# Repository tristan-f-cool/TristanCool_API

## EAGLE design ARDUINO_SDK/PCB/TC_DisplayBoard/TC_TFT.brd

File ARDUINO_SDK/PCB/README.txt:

$$$$$$$$$$$$$$$$$$$$$$$$$$$$$$$$$$$$$$$$$$$$$$$$$$$$$$$$$$$$$$$$$$$$$$$$$$$$$$$$$$$$$$$$$
$		     		Tristan Cool Master API 				$
$	            	         PCB Proto Dev board					$
$				     Arduino SDK					$
$$$$$$$$$$$$$$$$$$$$$$$$$$$$$$$$$$$$$$$$$$$$$$$$$$$$$$$$$$$$$$$$$$$$$$$$$$$$$$$$$$$$$$$$$
...\TristanCool_API\ARDUINO_SDK\PCB

_________________________________________________________________________________________
~~~ VERSION ~~~~~ DATE ~~~~~~~~ AUTHOR ~~~~~~~~~~~~~~~~~~~ NOTE ~~~~~~~~~~~~~~~~~~~~~~~~~
_________________________________________________________________________________________
     0.0       2020_10_17	Tristan Cool		Initial project creation

_________________________________________________________________________________________

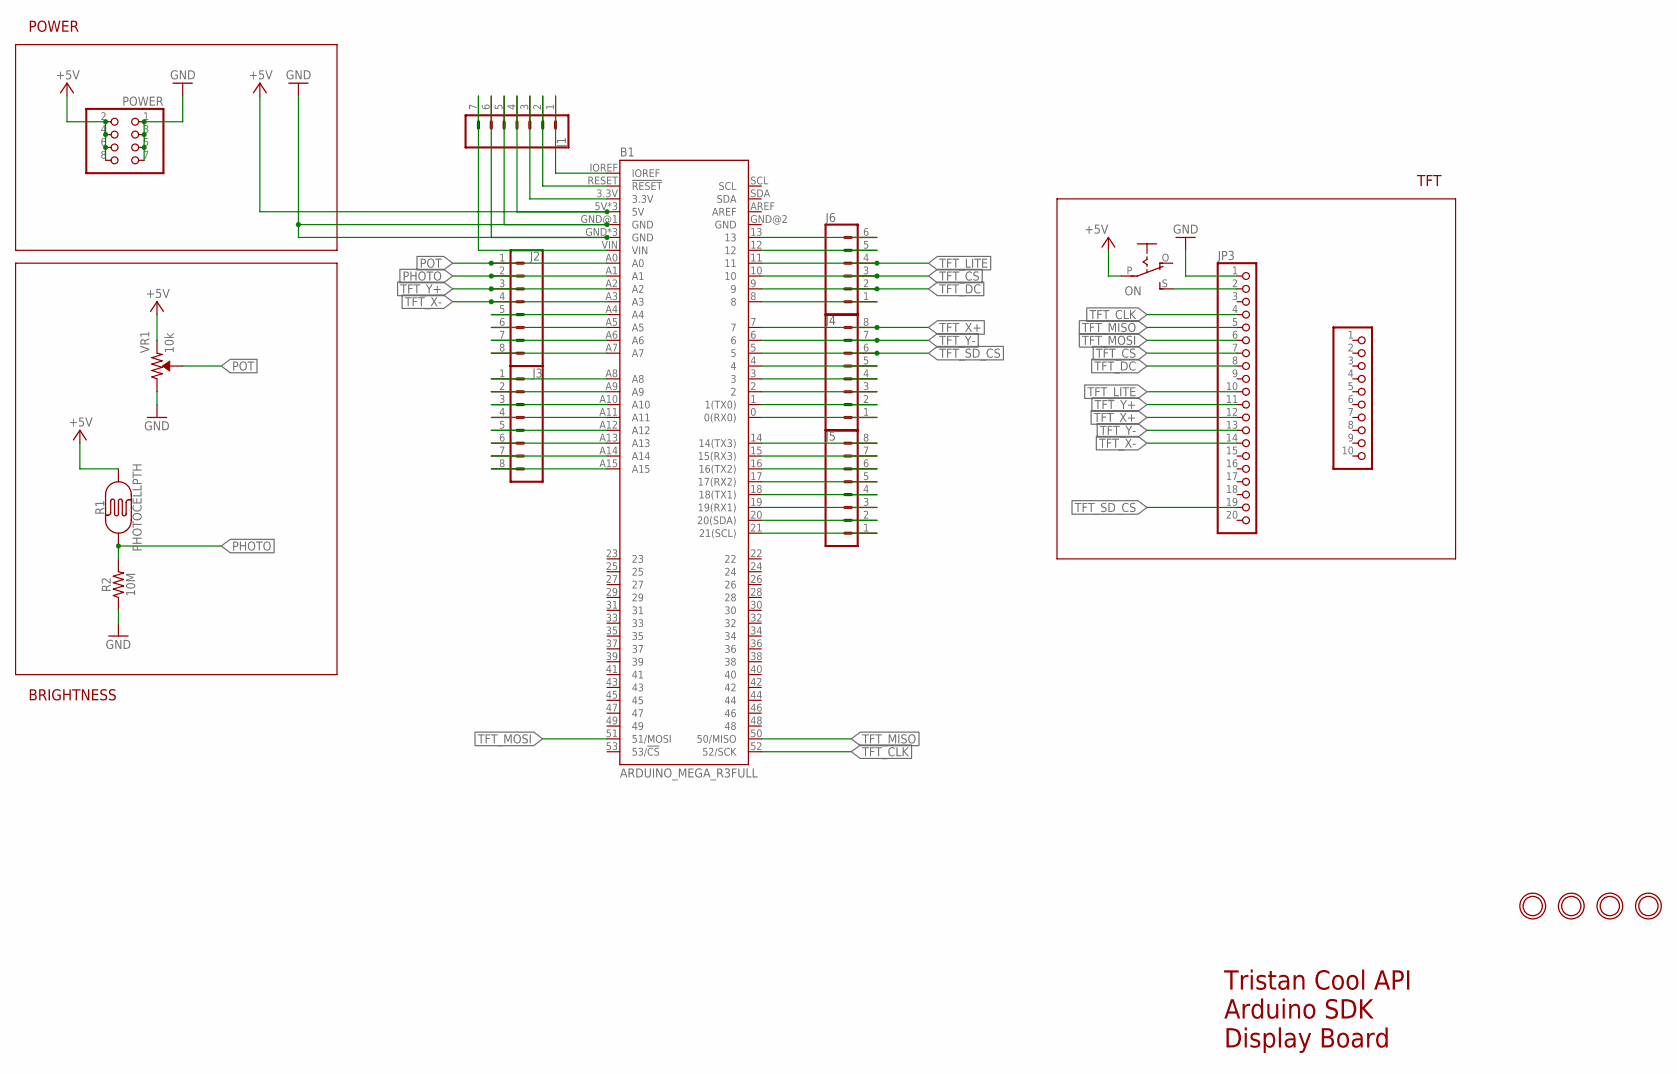
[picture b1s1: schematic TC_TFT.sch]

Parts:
B1: ARDUINO_MEGA_R3FULL; ARDUINO_MEGA_NO_SILK
J1: CONN_07; 1X07
J2, J3, J4, J5: CONN_08"; 1X08
J6: CONN_06SILK_FEMALE_PTH; 1X06
JP3: HEADER-1X20ROUND; 1X20_ROUND
ON: EG1218S; EG1218
POWER: PINHD-2X4; 2X04
R1: PHOTOCELLPTH; PHOTOCELL
R2: 10M; 0603
U$1, U$2, U$3, U$4: MOUNTINGHOLE3.0THIN; MOUNTINGHOLE_3.0_PLATEDTHIN
U$5: PINHD-1X10; 1X10-BIG
VR1: 10k; TRIMPOT-PTH-3386U

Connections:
+5V: B1.5V, B1.5V@1 (5V), B1.5V@2 (5V), J1.4, ON.P, POWER.2, POWER.4, POWER.6, POWER.8, R1.2, VR1.1 (CCW)
GND: B1.GND, B1.GND@1 (GND), B1.GND@3 (GND), B1.GND@4 (GND), J1.5, J1.6, JP3.1, POWER.1, POWER.3, POWER.5, POWER.7, R2.1, VR1.3 (CW)
unnamed: JP3.2, ON.S
unnamed: B1.IOREF, J1.1
unnamed: B1.RESET (!RESET), J1.2
unnamed: B1.3.3V, J1.3
unnamed: B1.VIN, J1.7
unnamed: B1.A4, J2.5
unnamed: B1.A5, J2.6
unnamed: B1.A6, J2.7
unnamed: B1.A7, J2.8
unnamed: B1.A8, J3.1
unnamed: B1.A9, J3.2
unnamed: B1.A10, J3.3
unnamed: B1.A11, J3.4
unnamed: B1.A12, J3.5
unnamed: B1.A13, J3.6
unnamed: B1.A14, J3.7
unnamed: B1.A15, J3.8
unnamed: B1.8, J6.1
unnamed: B1.12, J6.5
unnamed: B1.13, J6.6
unnamed: B1.4, J4.5
unnamed: B1.3, J4.4
unnamed: B1.2, J4.3
unnamed: B1.1 (1(TX0)), J4.2
unnamed: B1.0 (0(RX0)), J4.1
unnamed: B1.14 (14(TX3)), J5.8
unnamed: B1.15 (15(RX3)), J5.7
unnamed: B1.16 (16(TX2)), J5.6
unnamed: B1.17 (17(RX2)), J5.5
unnamed: B1.18 (18(TX1)), J5.4
unnamed: B1.19 (19(RX1)), J5.3
unnamed: B1.20 (20(SDA)), J5.2
unnamed: B1.21 (21(SCL)), J5.1
PHOTO: B1.A1, J2.2, R1.1, R2.2
POT: B1.A0, J2.1, VR1.2 (WIPER)
TFT_CLK: B1.52 (52/SCK), JP3.4
TFT_CS: B1.10, J6.3, JP3.7
TFT_DC: B1.9, J6.2, JP3.8
TFT_LITE: B1.11, J6.4, JP3.10
TFT_MISO: B1.50 (50/MISO), JP3.5
TFT_MOSI: B1.51 (51/MOSI), JP3.6
TFT_SD_CS: B1.5, J4.6, JP3.19
TFT_X+: B1.7, J4.8, JP3.12
TFT_X-: B1.A3, J2.4, JP3.14
TFT_Y+: B1.A2, J2.3, JP3.11
TFT_Y-: B1.6, J4.7, JP3.13

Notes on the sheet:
POWER
BRIGHTNESS
TFT
Tristan Cool API Arduino SDK Display Board

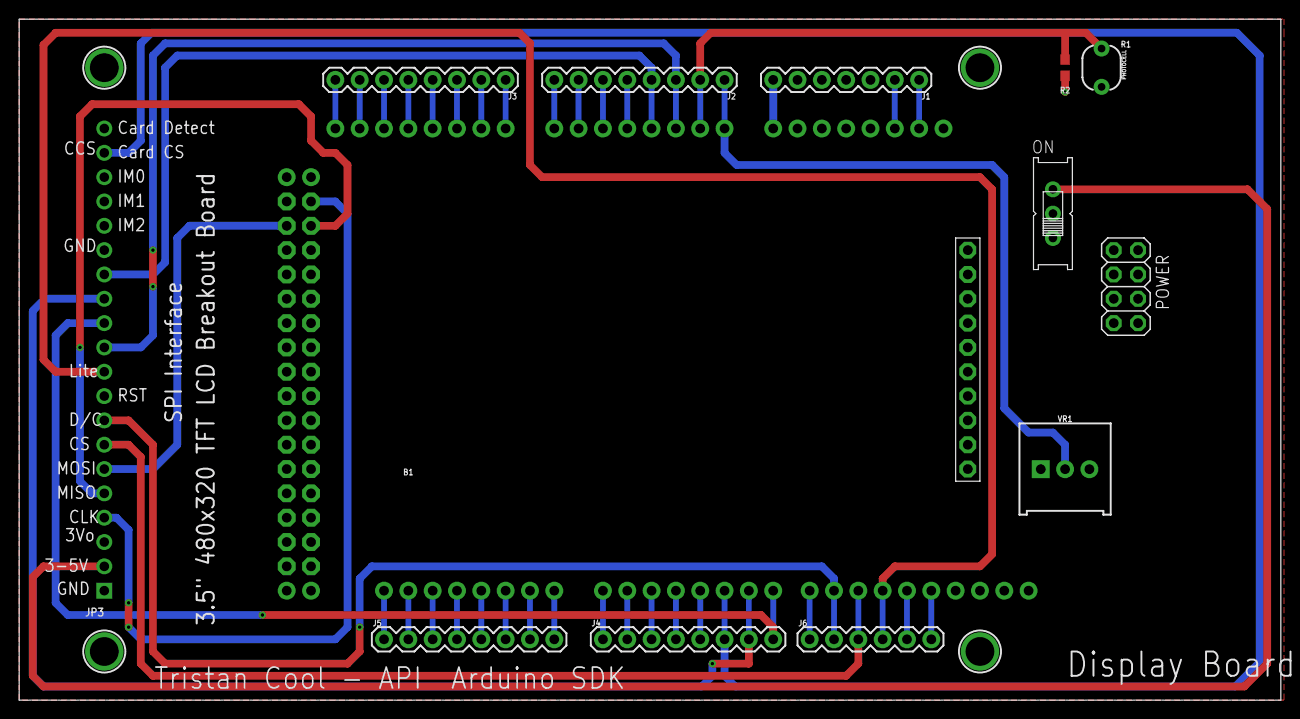
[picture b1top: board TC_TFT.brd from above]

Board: 2 copper layers, 131.8 x 71.1 mm, 18 parts (0 on the bottom side), 48 nets.

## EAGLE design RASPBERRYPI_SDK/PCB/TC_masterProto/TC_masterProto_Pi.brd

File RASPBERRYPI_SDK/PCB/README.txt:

$$$$$$$$$$$$$$$$$$$$$$$$$$$$$$$$$$$$$$$$$$$$$$$$$$$$$$$$$$$$$$$$$$$$$$$$$$$$$$$$$$$$$$$$$
$		     		Tristan Cool API PCB					$
$	            	      Master PCB Proto Dev board				$
$			          Raspberry PI SDK					$
$$$$$$$$$$$$$$$$$$$$$$$$$$$$$$$$$$$$$$$$$$$$$$$$$$$$$$$$$$$$$$$$$$$$$$$$$$$$$$$$$$$$$$$$$
...\TristanCool_API\RASPBERRYPI_SDK\PCB

_________________________________________________________________________________________
~~~ VERSION ~~~~~ DATE ~~~~~~~~ AUTHOR ~~~~~~~~~~~~~~~~~~~ NOTE ~~~~~~~~~~~~~~~~~~~~~~~~~
_________________________________________________________________________________________
     0.0       2020_10_17	Tristan Cool		Initial project creation

_________________________________________________________________________________________

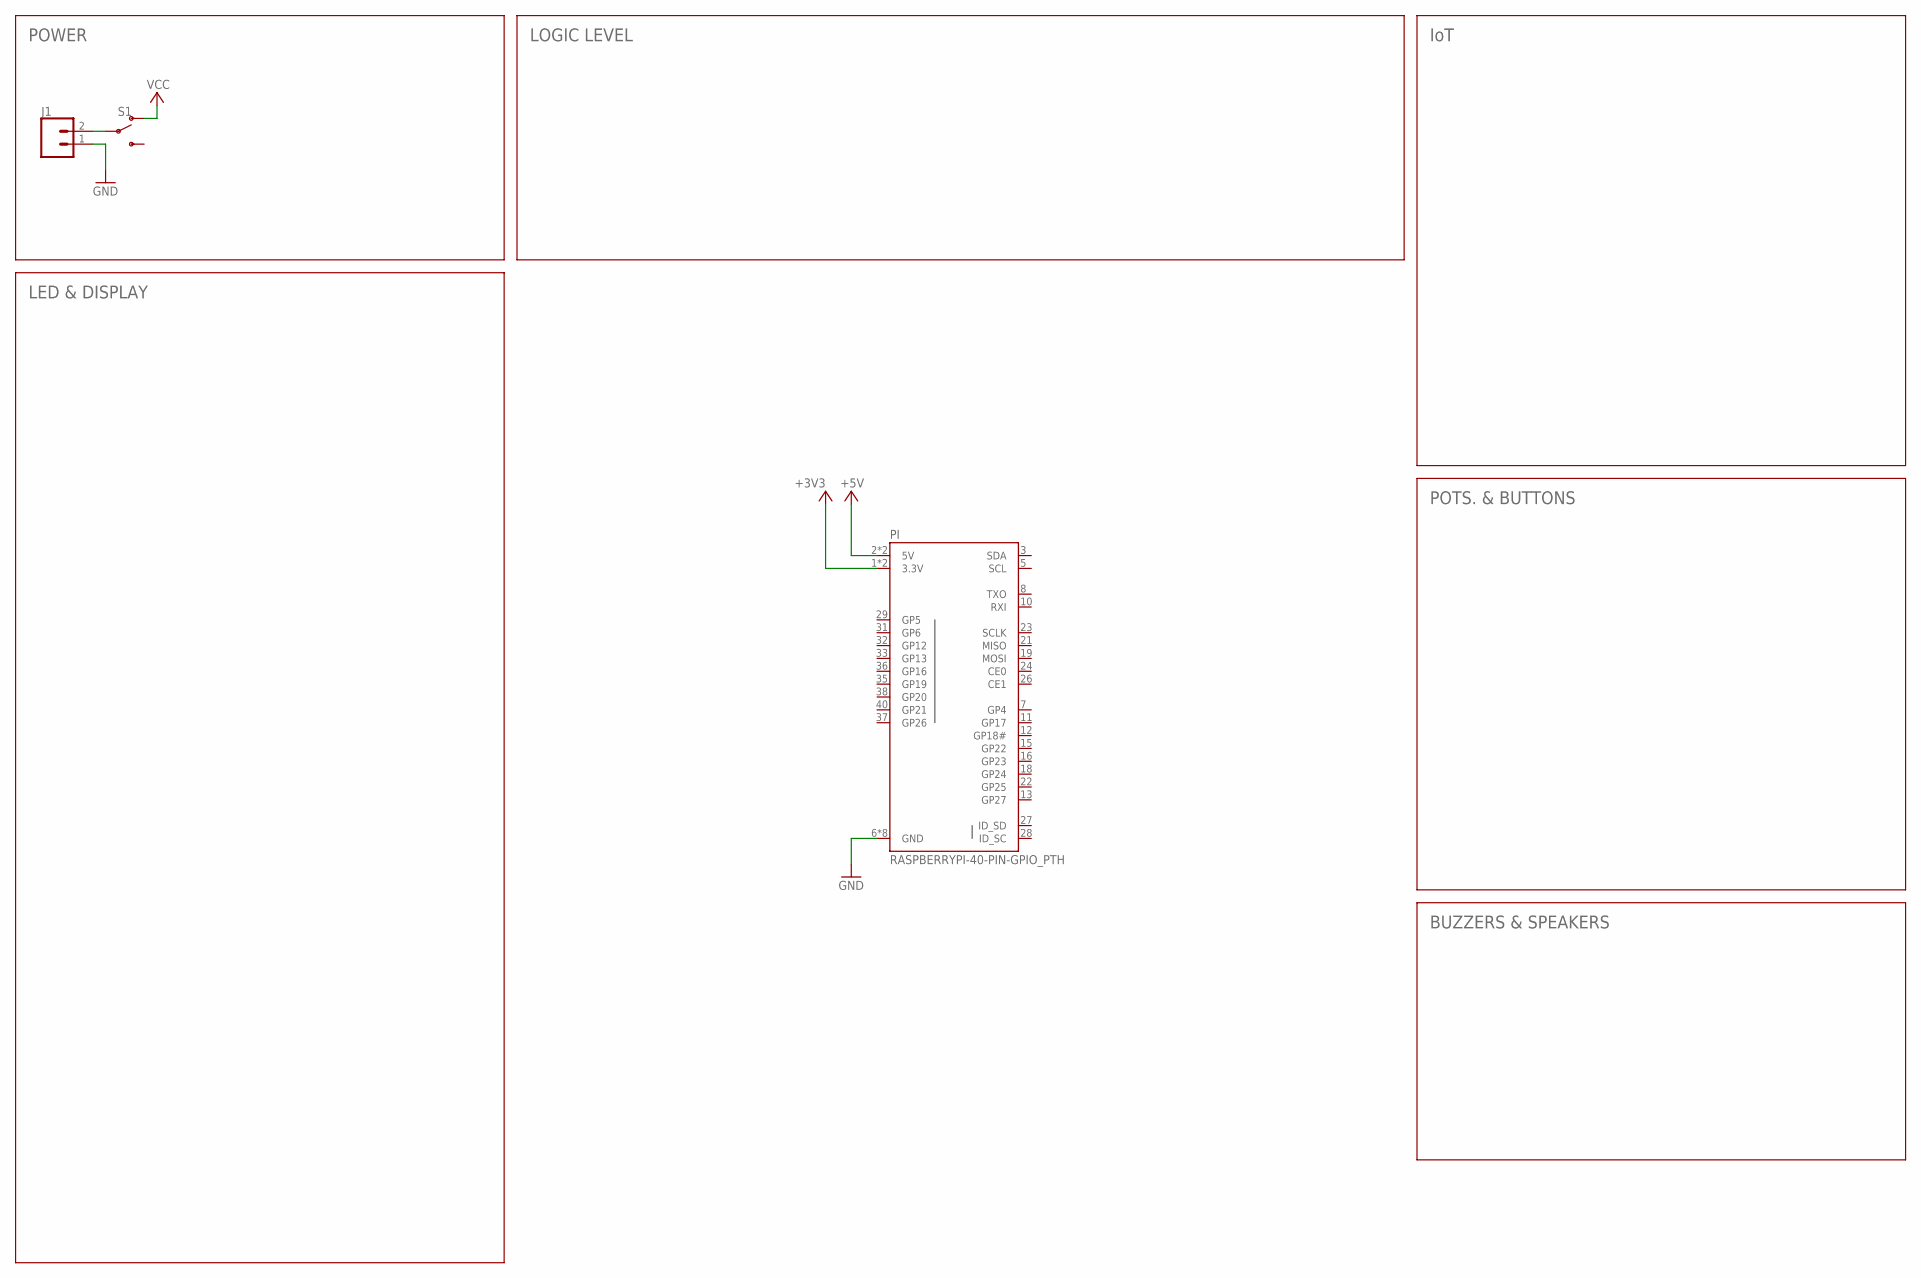
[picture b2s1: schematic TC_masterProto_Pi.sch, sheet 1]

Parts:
J1: CONN_023.5MM_LOCK; SCREWTERMINAL-3.5MM-2_LOCK
PI: RASPBERRYPI-40-PIN-GPIO_PTH; 2X20_SHROUDED
S1: SWITCH-SPDT-PTH-11.6X4.0MM-LOCK; SWITCH_SPDT_PTH_11.6X4.0MM_LOCK

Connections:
+3V3: PI.1 (3.3V), PI.17 (3.3V)
+5V: PI.2 (5V), PI.4 (5V)
GND: J1.1, PI.6 (GND), PI.9 (GND), PI.14 (GND), PI.20 (GND), PI.25 (GND), PI.30 (GND), PI.34 (GND), PI.39 (GND)
unnamed: J1.2, S1.2
VCC: S1.1 (O)

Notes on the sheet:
POWER
LED & DISPLAY
IoT
POTS. & BUTTONS
BUZZERS & SPEAKERS
LOGIC LEVEL

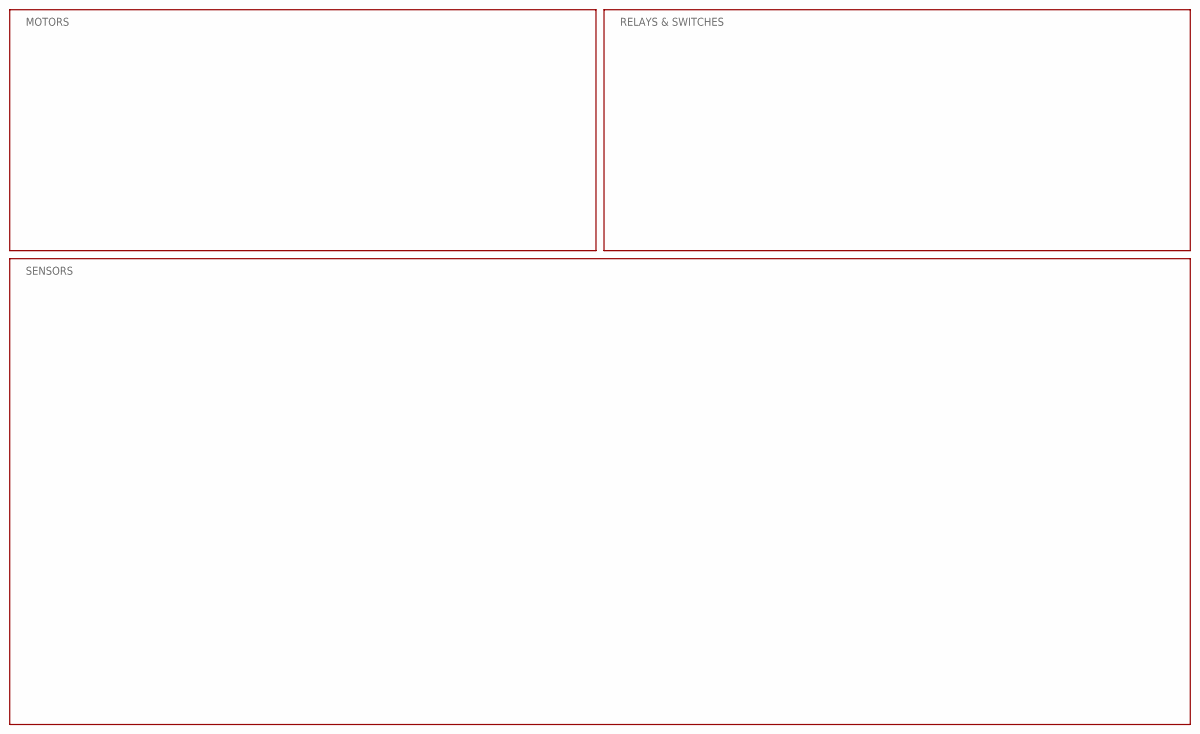
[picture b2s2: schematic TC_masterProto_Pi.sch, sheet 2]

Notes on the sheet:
MOTORS
RELAYS & SWITCHES
SENSORS

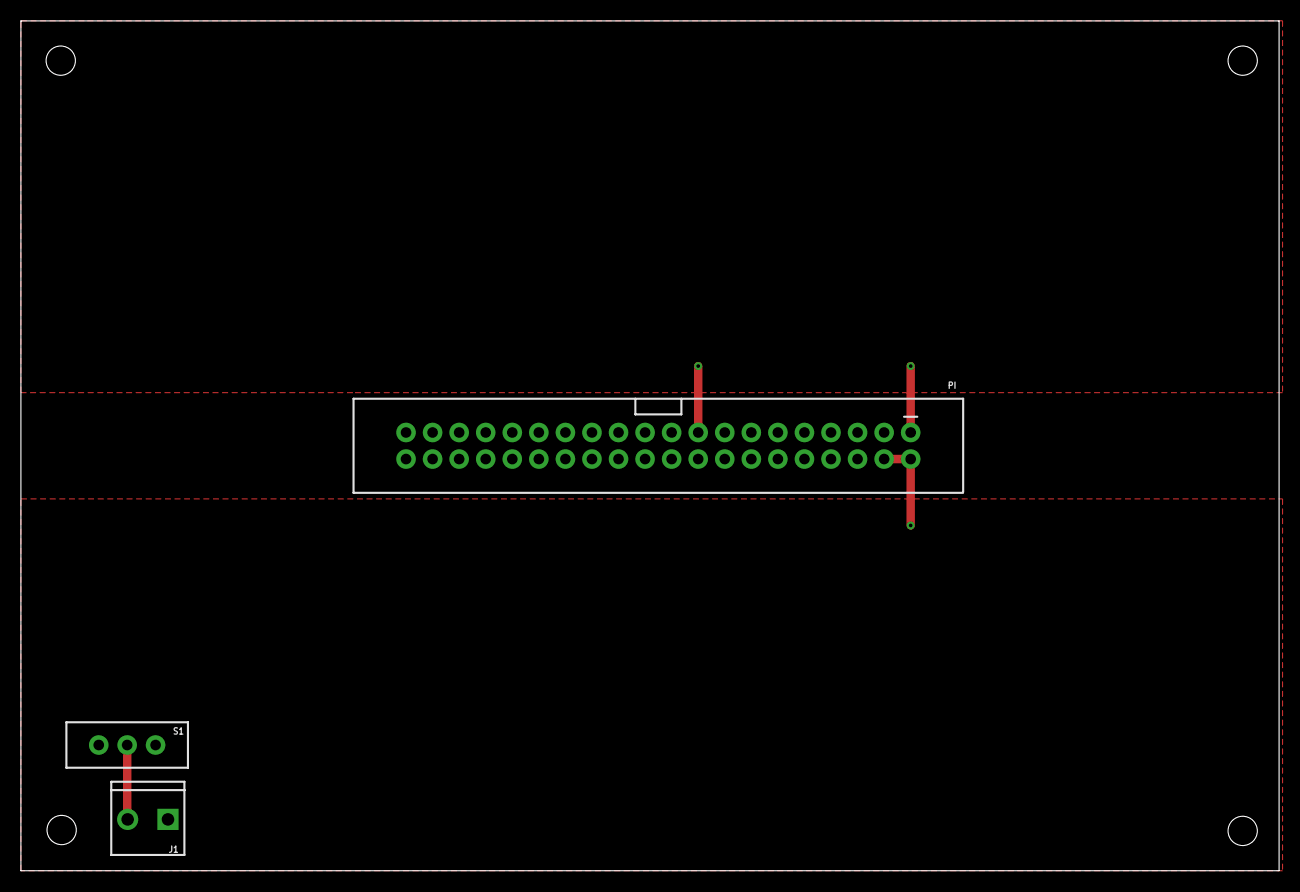
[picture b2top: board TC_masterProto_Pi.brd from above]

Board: 2 copper layers, 120.3 x 81.3 mm, 3 parts (0 on the bottom side), 4 nets.

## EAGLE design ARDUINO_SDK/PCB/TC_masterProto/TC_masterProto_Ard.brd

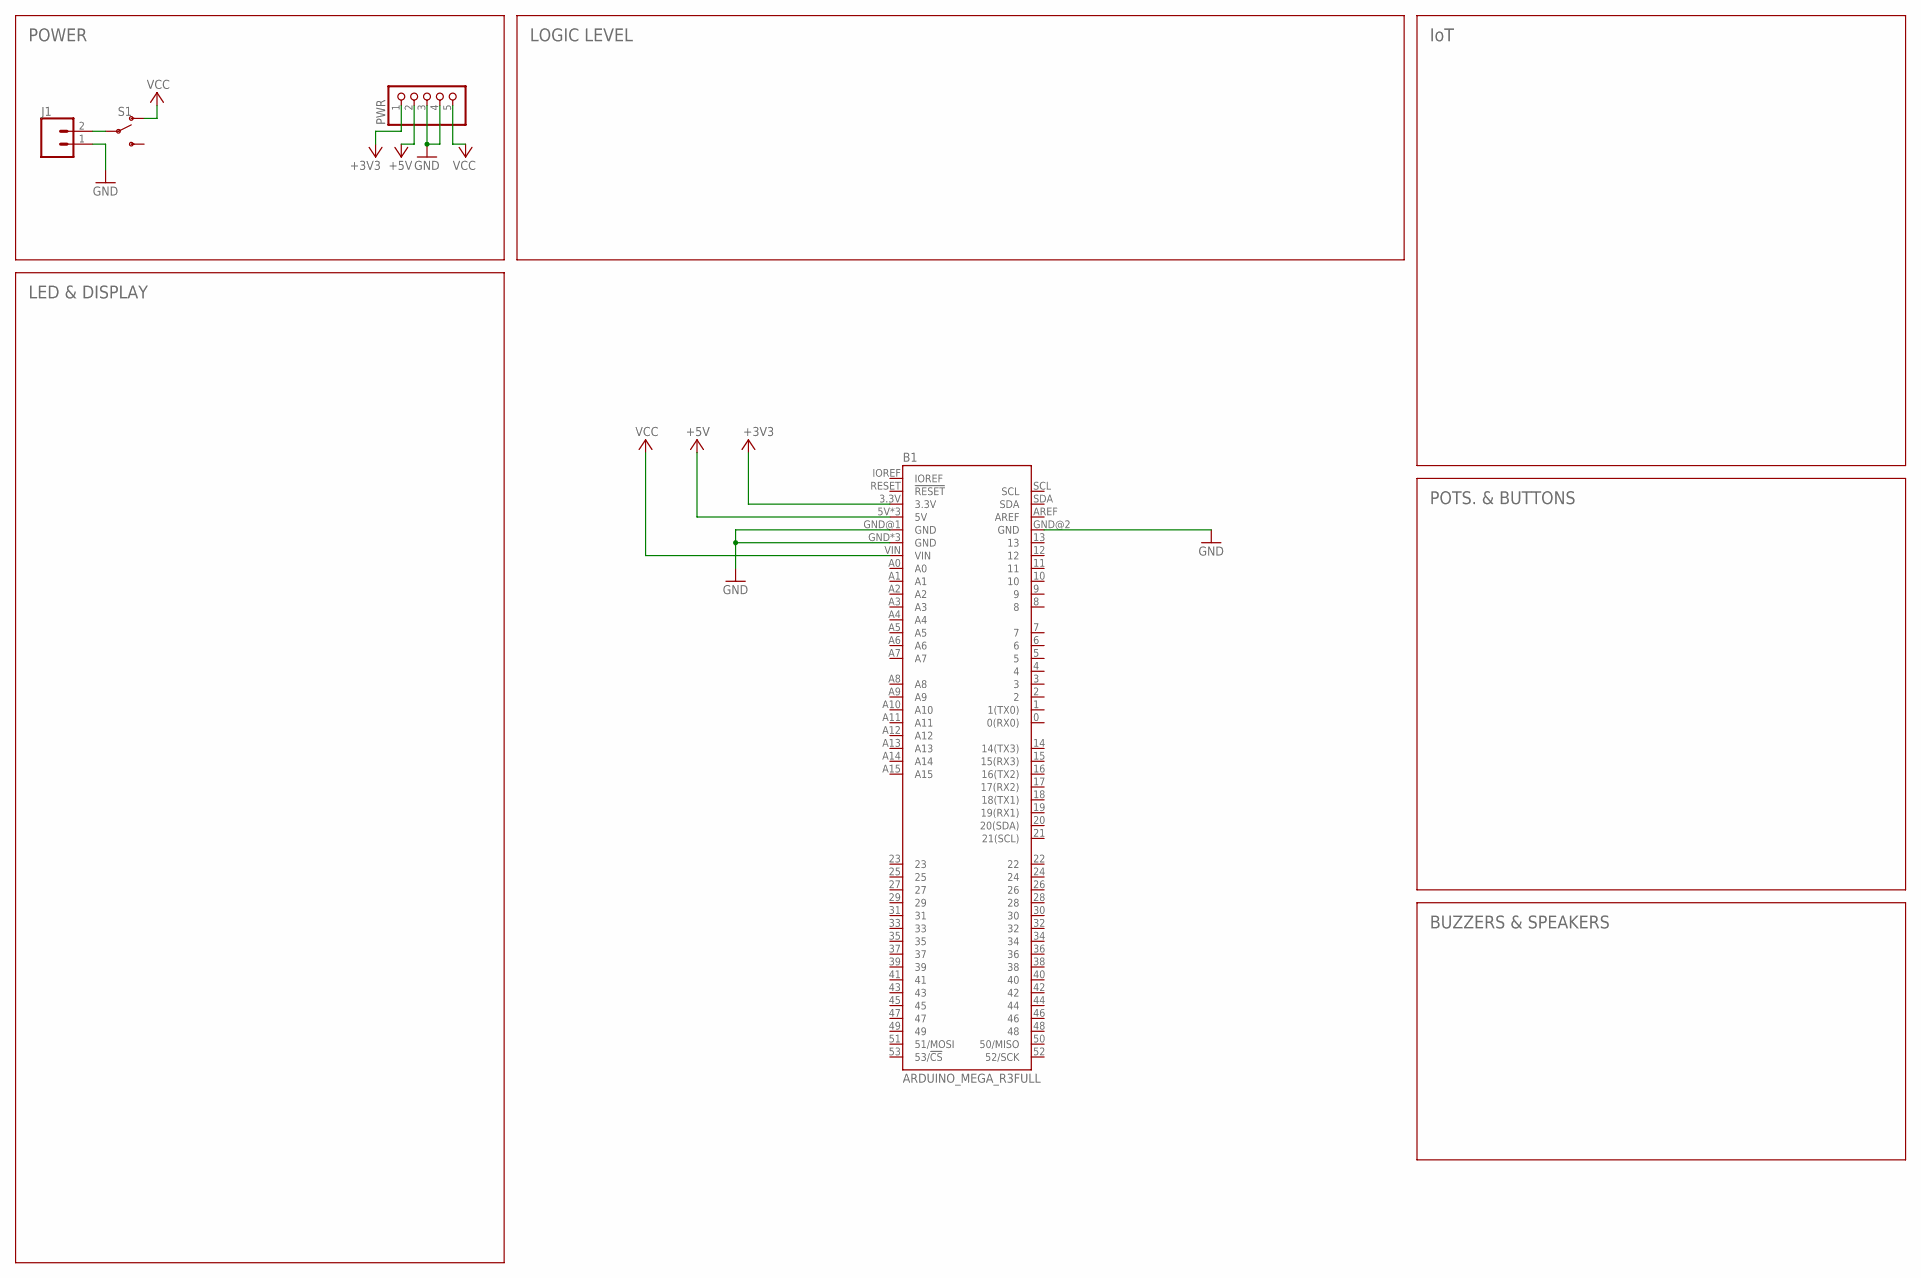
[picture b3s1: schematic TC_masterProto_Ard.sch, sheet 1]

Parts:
B1: ARDUINO_MEGA_R3FULL; ARDUINO_MEGA_NO_SILK
J1: CONN_023.5MM_LOCK; SCREWTERMINAL-3.5MM-2_LOCK
PWR: PINHD-1X5; 1X05
S1: SWITCH-SPDT-PTH-11.6X4.0MM-LOCK; SWITCH_SPDT_PTH_11.6X4.0MM_LOCK

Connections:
+3V3: B1.3.3V, PWR.1
+5V: B1.5V, B1.5V@1 (5V), B1.5V@2 (5V), PWR.2
GND: B1.GND, B1.GND@1 (GND), B1.GND@2 (GND), B1.GND@3 (GND), B1.GND@4 (GND), J1.1, PWR.3, PWR.4
unnamed: J1.2, S1.2
VCC: B1.VIN, PWR.5, S1.1 (O)

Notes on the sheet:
POWER
LED & DISPLAY
IoT
POTS. & BUTTONS
BUZZERS & SPEAKERS
LOGIC LEVEL

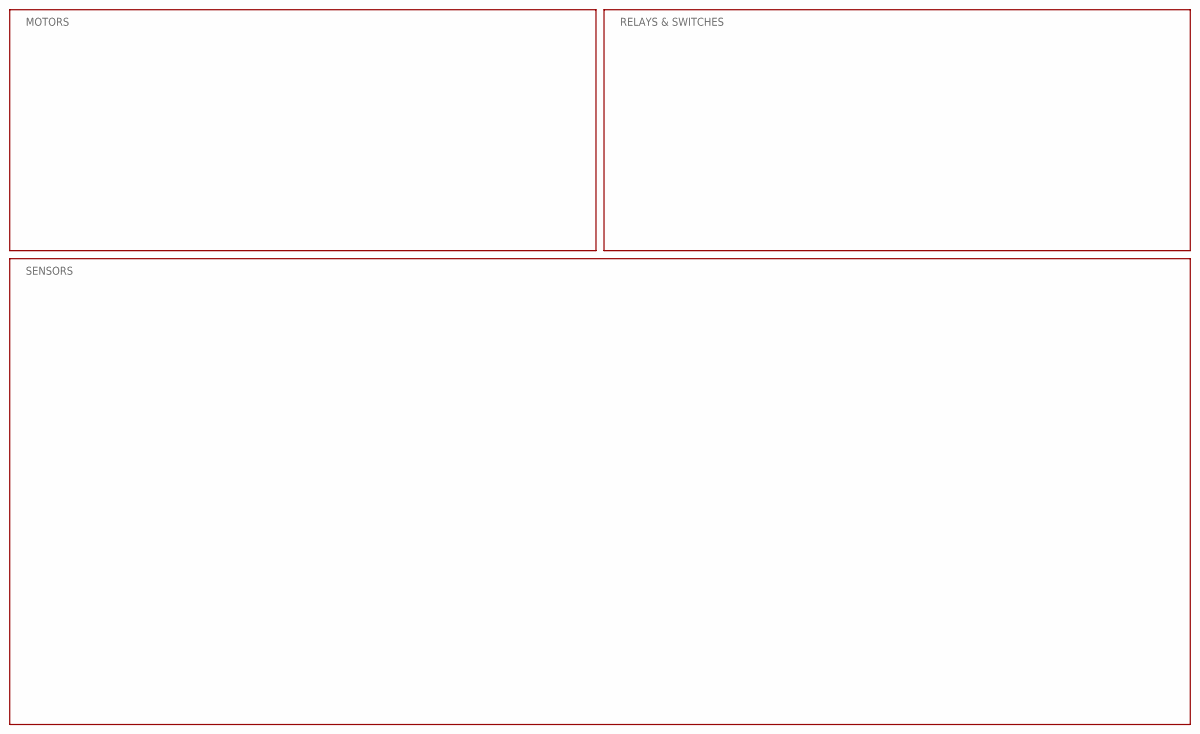
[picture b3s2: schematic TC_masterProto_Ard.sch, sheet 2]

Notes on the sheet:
MOTORS
RELAYS & SWITCHES
SENSORS

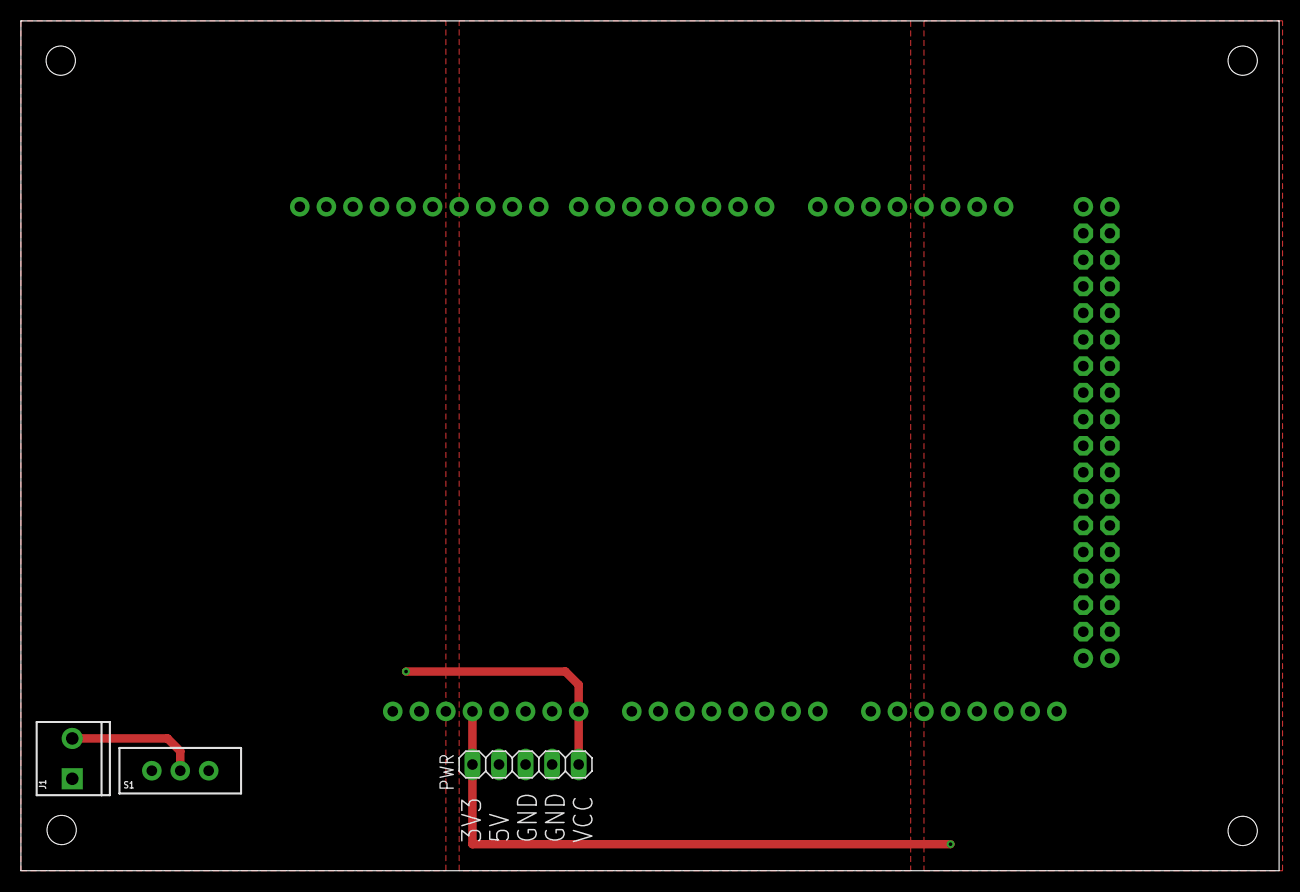
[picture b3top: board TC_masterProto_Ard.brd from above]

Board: 2 copper layers, 120.3 x 81.3 mm, 4 parts (0 on the bottom side), 5 nets.

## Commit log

2020-11-05 RELEASE RECORD created
2020-11-05 README created for HARDWARE
2020-11-05 Fritzing libraries added
2020-11-05 Fritzing template for breadboard prototyping hardware components
2020-11-05 README for Arduino default libraries
2020-11-05 Arduino default library: Adafruit Circuit Playground
2020-11-05 Arduino default library: Bridge
2020-11-05 Arduino default library: Esplora
2020-11-05 Arduino default library: Ethernet
2020-11-05 Arduino default library: Firmata
2020-11-05 Arduino default library: GSM
2020-11-05 Arduino default library: Keyboard
2020-11-05 Arduino default library: Liquid Crystal
2020-11-05 Arduino default library: Mouse
2020-11-05 Arduino default library: Robot Control
2020-11-05 Arduino default library: Robot Motor
2020-11-05 Arduino default library: Robot IR Remote
2020-11-05 Arduino default library: SD
2020-11-05 Arduino default library: Servo
2020-11-05 Arduino default library: SpacebrewYun
2020-11-05 Arduino default library: Stepper
2020-11-05 Arduino default library: Temboo
2020-11-05 Arduino default library: TFT
2020-11-05 Arduino default library: WiFi
2020-11-05 Arduino Firmware user libraries
2020-11-05 Arduino development firmware
2020-11-05 README PCB Arduino SDK
2020-11-05 Arduino PCB Eagle custom design blocks
2020-11-05 PCB logos
2020-11-05 Arduino SDK PCB Eagle project
2020-11-05 Eagle PCB libraries
2020-11-05 README for HARDWARE Raspberry Pi SDK
2020-11-05 Fritizing libraries
2020-11-05 Fritizing template file
2020-11-05 Raspberry Pi firmware bootloader
2020-11-05 Raspberry Pi firmware code
2020-11-05 Library firmware dependencies
2020-11-05 User defined peripheral libraries
2020-11-05 README PCB Raspberry Pi SDK
2020-11-05 Eagle PCB custom design blocks
2020-11-05 Raspberry Pi SDK Eagle PCB project
2021-01-25 HX8357 TFT library
2021-01-25 TouchScreen library
2021-01-25 SD Fat memory card library
2021-01-25 TFT library
2021-01-25 TFT breadboard + protoboard design
2021-01-25 TFT Display board PCB + Design Block

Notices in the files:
parts and their libraries:
SparkFun-Boards: Licensing: Creative Commons ShareAlike 4.0 International - https://creativecommons.org/licenses/by-sa/4.0
